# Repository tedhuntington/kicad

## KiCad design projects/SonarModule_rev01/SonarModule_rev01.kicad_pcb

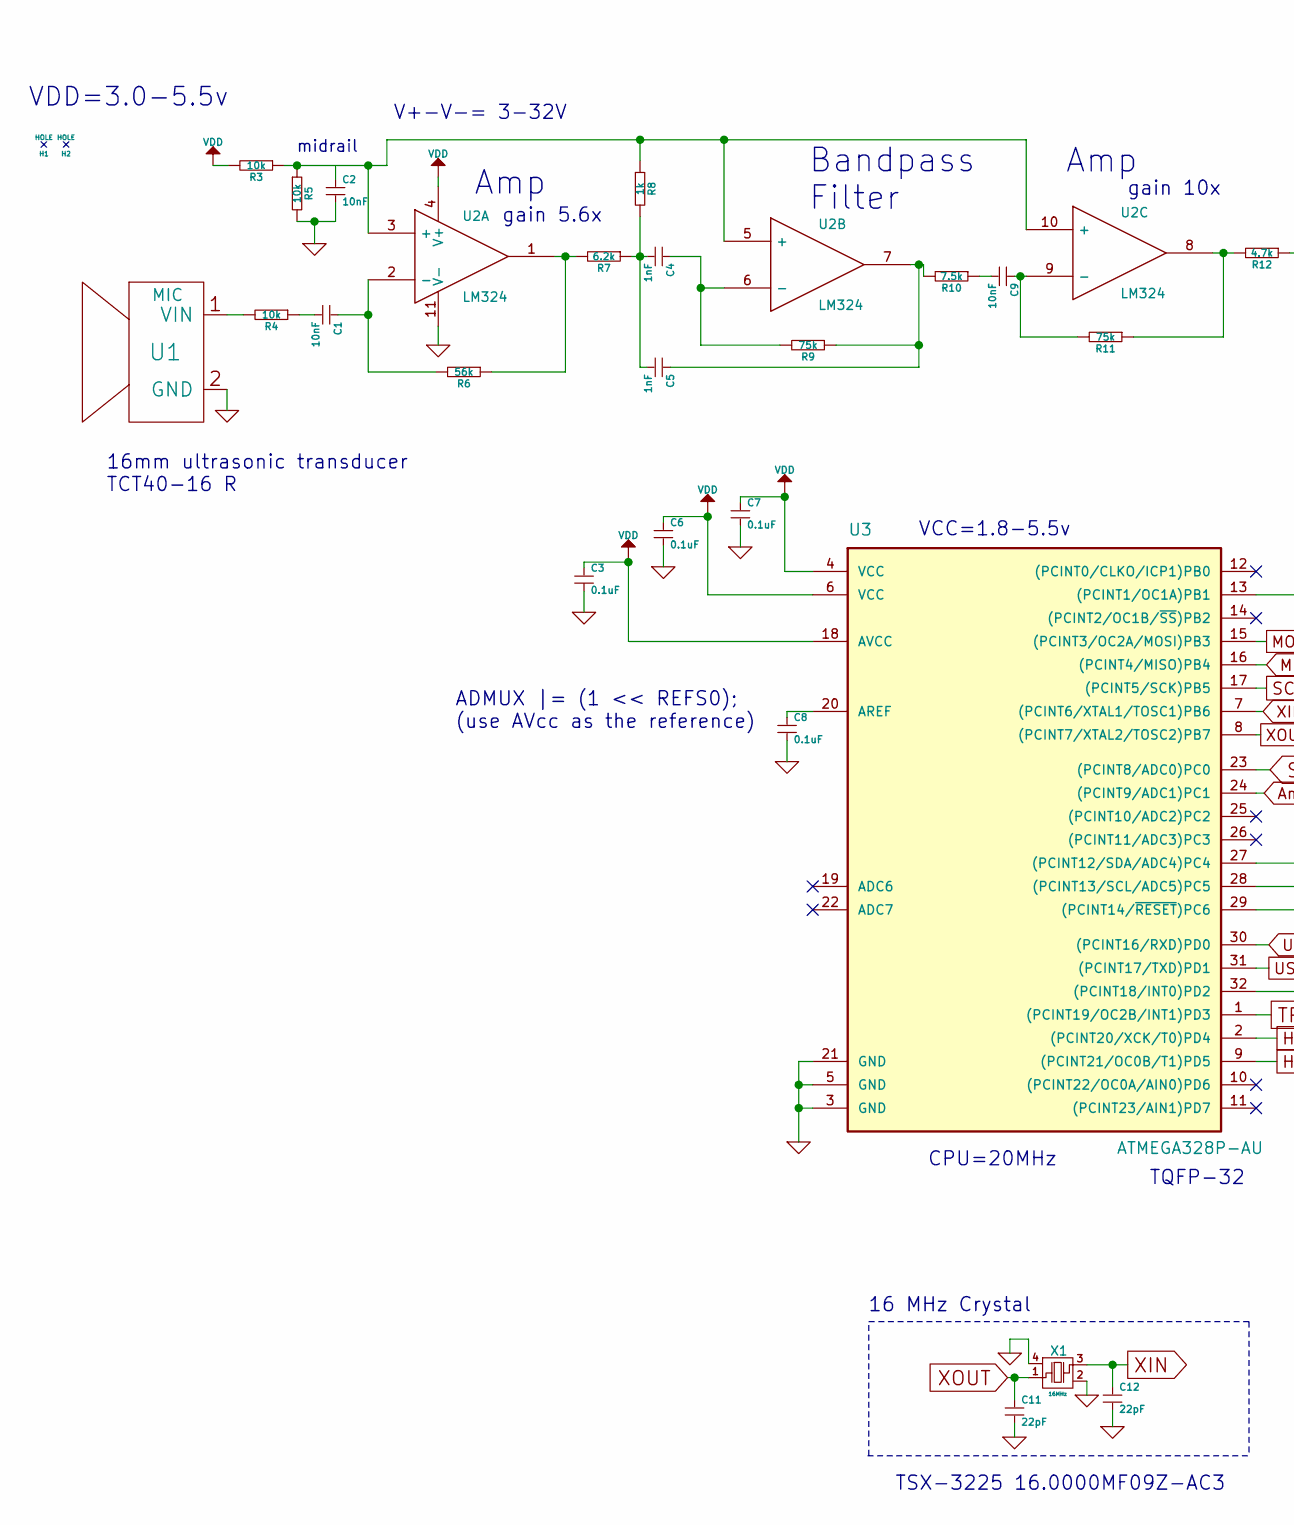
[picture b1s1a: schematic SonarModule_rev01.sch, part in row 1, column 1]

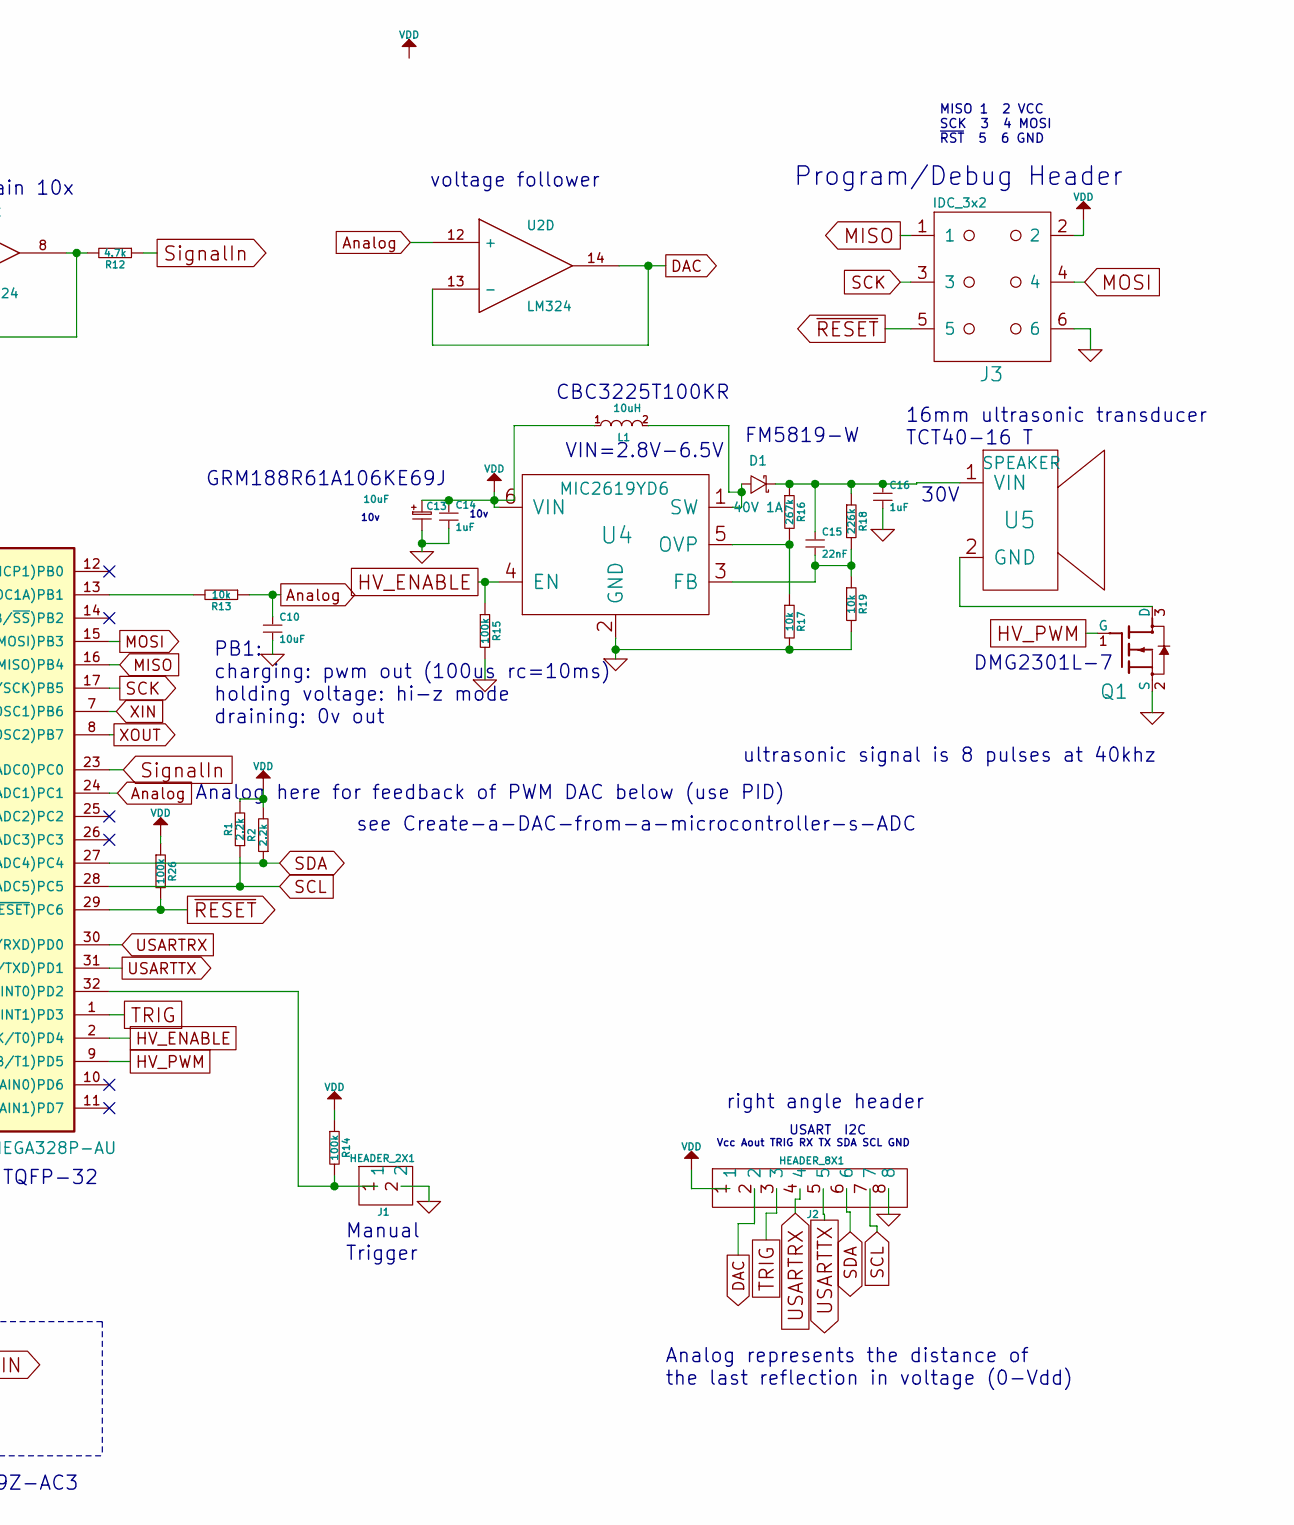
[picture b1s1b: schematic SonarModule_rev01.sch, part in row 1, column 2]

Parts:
C1, C2, C9: 10nF; TED_SM1608_0603_C
C3, C6, C7, C8: 0.1uF; TED_SM1608_0603_C
C4, C5: 1nF; TED_SM1608_0603_C
C10, C13: 10uF; TED_SM1608_0603_C
C11, C12: 22pF; TED_SM1608_0603_C
C14, C16: 1uF; TED_SM1608_0603_C
C15: 22nF; TED_SM1608_0603_C
D1: 40V 1A; TED_DO-214AC
H1, H2: HOLE; TED_Hole_3mm
J1: HEADER_2X1; TED_HEADER_2x1
J2: HEADER_8X1; TED_HEADER_8x1
J3: IDC_3x2; TED_HEADER_3x2
L1: 10uH; L_3225_1210
Q1: NMOSFET_GSD; SOT-23
R1, R2: 2.2k; TED_SM0603_R
R3, R4, R5, R13, R17, R19: 10k; TED_SM0603_R
R6: 56k; TED_SM0603_R
R7: 6.2k; TED_SM0603_R
R8: 1k; TED_SM0603_R
R9, R11: 75k; TED_SM0603_R
R10: 7.5k; TED_SM0603_R
R12: 4.7k; TED_SM0603_R
R14, R15, R26: 100k; TED_SM0603_R
R16: 267k; TED_SM0603_R
R18: 226k; TED_SM0603_R
U1: MIC; Transducer_16mm
U2: LM324; SOIC-14_3.9x8.7mm_Pitch1.27mm
U3: ATMEGA328P-AU; TQFP-32_7x7mm_Pitch0.8mm
U4: MIC2619YD6; SOT-23-6
U5: SPEAKER; Transducer_16mm
X1: 16MHz; TED_crystal_FA-20H

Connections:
Analog: C10.1, R13.1, U2.12 (+), U3.24 ((PCINT9/ADC1)PC1)
DAC: J2.2, U2.13 (-), U2.14
GND: C2.2, C3.2, C6.2, C7.2, C8.2, C10.2, C11.2, C12.2, C13.2, C14.2, C16.2, J1.2, J2.8, J3.6, Q1.2 (S), R5.2, R15.2, R17.2, R19.2, U1.2 (GND), U2.11 (V-), U3.3 (GND), U3.5 (GND), U3.21 (GND), U4.2 (GND), X1.2, X1.4
HV_ENABLE: R15.1, U3.2 ((PCINT20/XCK/T0)PD4), U4.4 (EN)
HV_PWM: Q1.1 (G), U3.9 ((PCINT21/OC0B/T1)PD5)
MISO: J3.1, U3.16 ((PCINT4/MISO)PB4)
MOSI: J3.4, U3.15 ((PCINT3/OC2A/MOSI)PB3)
unnamed: C1.1, R6.2, U2.2 (-)
unnamed: C1.2, R4.1
unnamed: C4.1, R9.2, U2.6 (-)
unnamed: C4.2, C5.2, R7.1, R8.2
unnamed: C5.1, R9.1, R10.2, U2.7
unnamed: C8.1, U3.20 (AREF)
unnamed: C9.1, R11.2, U2.9 (-)
unnamed: C9.2, R10.1
unnamed: C15.1, C16.1, D1.2 (K), R16.1, R18.1, U5.1 (VIN)
unnamed: C15.2, R18.2, R19.1, U4.3 (FB)
unnamed: D1.1 (A), L1.2, U4.1 (SW)
unnamed: J1.1, R14.2, U3.32 ((PCINT18/INT0)PD2)
unnamed: Q1.3 (D), U5.2 (GND)
unnamed: R3.1, R5.1, R8.1, U2.3 (+), U2.5 (+), U2.10 (+)
unnamed: R4.2, U1.1 (VIN)
unnamed: R6.1, R7.2, U2.1
unnamed: R11.1, R12.2, U2.8
unnamed: R13.2, U3.13 ((PCINT1/OC1A)PB1)
unnamed: R16.2, R17.1, U4.5 (OVP)
SCK: J3.3, U3.17 ((PCINT5/SCK)PB5)
SCL: J2.7, R1.1, U3.28 ((PCINT13/SCL/ADC5)PC5)
SDA: J2.6, R2.1, U3.27 ((PCINT12/SDA/ADC4)PC4)
SignalIn: R12.1, U3.23 ((PCINT8/ADC0)PC0)
TRIG: J2.3, U3.1 ((PCINT19/OC2B/INT1)PD3)
USARTRX: J2.4, U3.30 ((PCINT16/RXD)PD0)
USARTTX: J2.5, U3.31 ((PCINT17/TXD)PD1)
VDD: C3.1, C6.1, C7.1, C13.1, C14.1, J2.1, J3.2, L1.1, R1.2, R2.2, R3.2, R14.1, R26.1, U2.4 (V+), U3.4 (VCC), U3.6 (VCC), U3.18 (AVCC), U4.6 (VIN)
XIN: C12.1, U3.7 ((PCINT6/XTAL1/TOSC1)PB6), X1.3
XOUT: C11.1, U3.8 ((PCINT7/XTAL2/TOSC2)PB7), X1.1
~RESET~: J3.5, R26.2, U3.29 ((PCINT14/~RESET~)PC6)

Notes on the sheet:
VDD=3.0-5.5v
16 MHz Crystal
USART
MISO 1 2 VCC SCK 3 4 MOSI ~RST~ 5 6 GND
Program/Debug Header
Vcc Aout TRIG RX TX SDA SCL GND
Manual Trigger
I2C
VIN=2.8V-6.5V
30V
Amp
Bandpass Filter
midrail
voltage follower
gain 5.6x
gain 10x
ultrasonic signal is 8 pulses at 40khz
Analog represents the distance of the last reflection in voltage (0-Vdd)
ADMUX |= (1 << REFS0); (use AVcc as the reference)
Analog here for feedback of PWM DAC below (use PID)
see Create-a-DAC-from-a-microcontroller-s-ADC
PB1: charging: pwm out (100us rc=10ms) holding voltage: hi-z mode draining: 0v out
right angle header
16mm ultrasonic transducer TCT40-16 T
16mm ultrasonic transducer TCT40-16 R
CBC3225T100KR
FM5819-W
GRM188R61A106KE69J
DMG2301L-7
CPU=20MHz
TQFP-32
VCC=1.8-5.5v
V+-V-= 3-32V
10v
TSX-3225 16.0000MF09Z-AC3

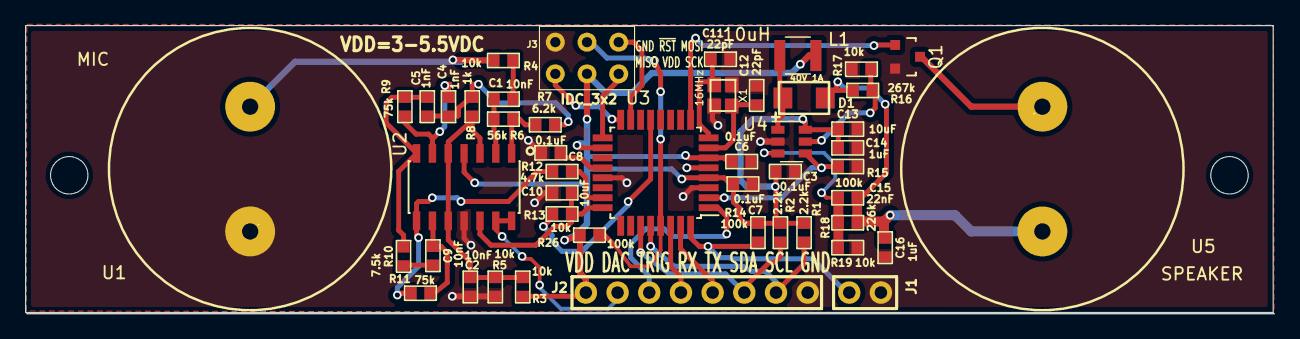
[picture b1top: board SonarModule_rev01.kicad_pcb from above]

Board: 2 copper layers, 100.0 x 23.0 mm, 50 parts (0 on the bottom side), 37 nets.

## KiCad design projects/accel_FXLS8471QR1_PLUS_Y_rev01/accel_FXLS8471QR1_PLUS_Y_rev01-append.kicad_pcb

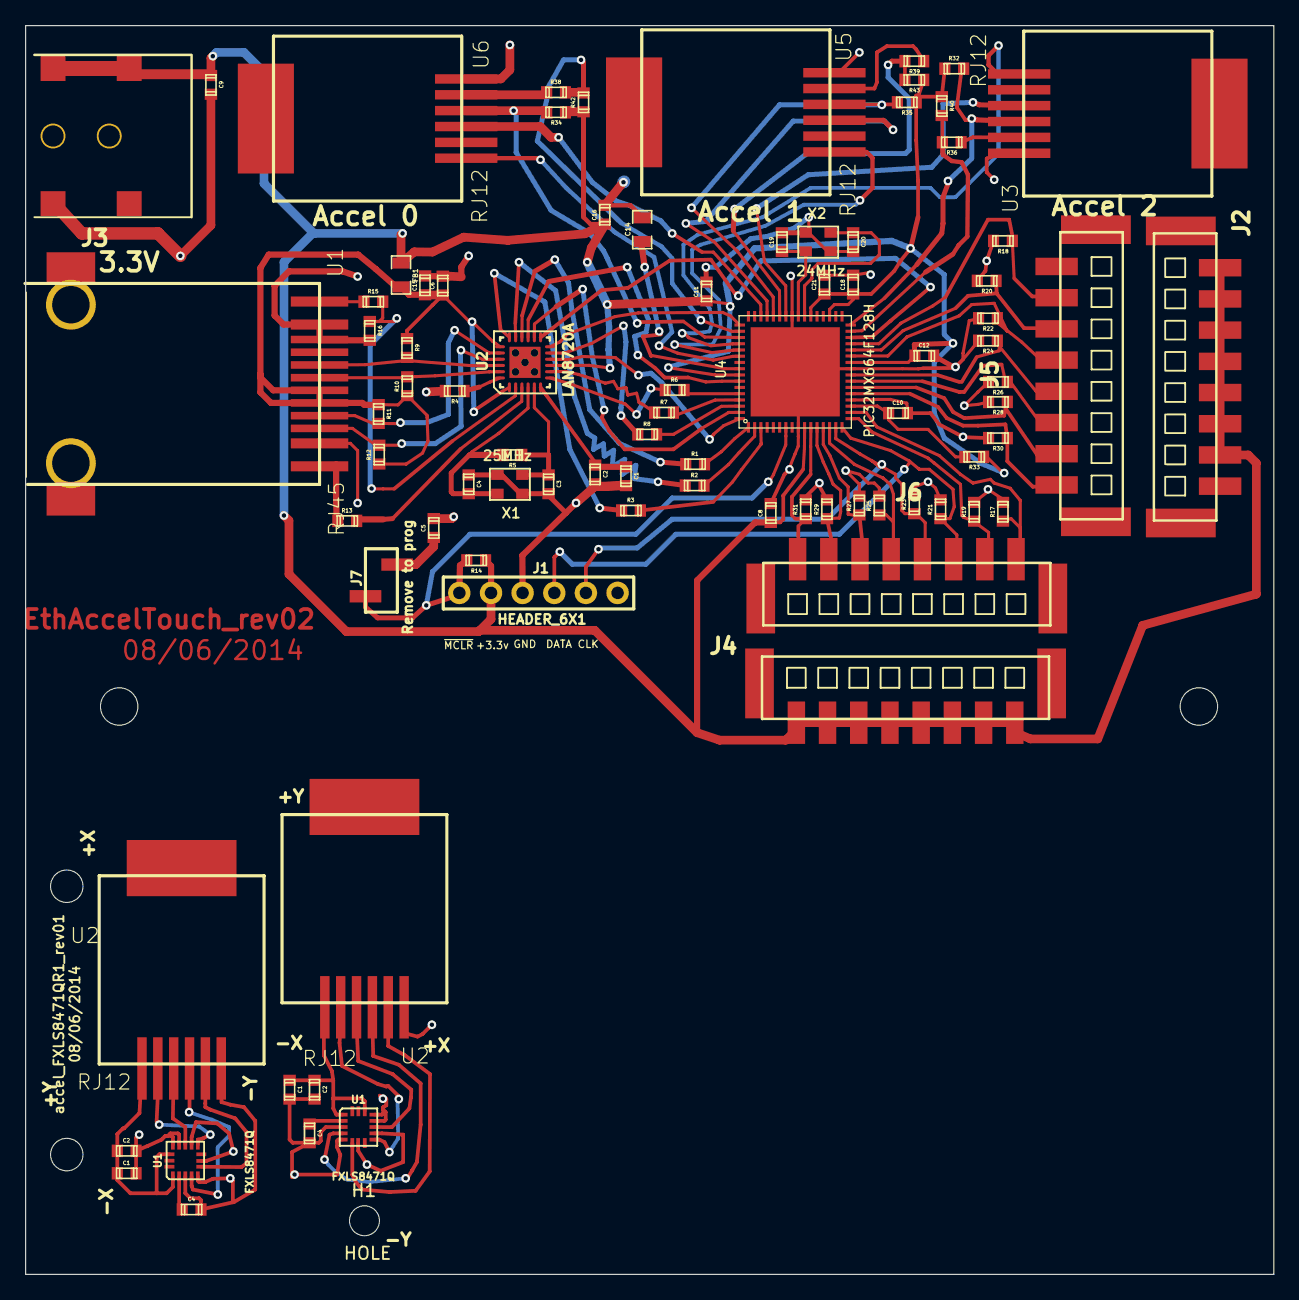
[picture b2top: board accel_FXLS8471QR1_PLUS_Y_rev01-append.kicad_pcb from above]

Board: 2 copper layers, 100.0 x 100.0 mm, 90 parts (0 on the bottom side), 73 nets.

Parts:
C1, C2#2, C2#3, C4#2, C4#3, C5, C6, C8, C10, C11, C12, C16, C18, C21: .1uF; TED_SM0603
C1#2, C1#3, C2, C15: 1uF; TED_SM0603
C3, C4: 18pF; TED_SM0603
C9: 4.7uF; TED_SM0603
C14: 10uF; TED_SM0805
C19, C20: 9pF; TED_SM0603
FB1: 500mA; TED_SM0805
H1, H2: HOLE; TED_Hole_3mm
H1#2, H2#2: HOLE; TED_Hole_2_6mm
H1#3: HOLE; TED_Hole_2_4mm
J1: HEADER_6X1; TED_HEADER_6x1_BOTTOM
J2, J4, J5, J6: TERMINAL_8X1; TED_Terminal_8x1_1814760
J3: DC_2.1MM; TED_DC_2.1mm_SMT
J7: Remove to prog; TED_JUMPER_2x1_SMD
R1, R2, R3, R6, R7, R8, R36, R38, R39: 33; TED_SM0603
R4: 12.1k 1%; TED_SM0603
R5: 1M; TED_SM0603
R9, R10, R11, R12: 49.9; TED_SM0603
R13, R15: 249; TED_SM0603
R14: 4.7k; TED_SM0603
R16: 10k 1%; TED_SM0603
R17, R18, R19, R20, R21, R22, R23, R24, R25, R26, R27, R28, R29, R30, R31: 1k; TED_SM0603
R32, R34, R35, R40, R42, R43: 2.4k; TED_SM0603
R33: 10; TED_SM0603
U1: RJ45; TED_RJ45_12pin_SMD
U1#2, U1#3: FXLS8471Q; TED_QFN16_3x5
U2: LAN8720A; TED_QFN24
U2#2, U2#3, U3, U5, U6: RJ12; TED_RJ12_855135002
U4: PIC32MX664F128H; TED_QFN64+1
X1: 25MHz; TED_crystal_TSX3225
X2: 24MHz; TED_crystal_TSX3225

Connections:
+3.3v: C8.1, C9.1, C11.1, C12.1, C16.1, C18.1, C21.1, FB1.1, J1.2, J2.1, J2.2, J2.3, J2.4, J2.5, J2.6, J2.7, J3.1, J4.1, J4.2, J4.3, J4.4, J4.5, J4.6, J4.7, J4.8, R14.1, R32.1, R33.1, R34.1, R35.1, R40.1, R42.1, R43.1, U2.9, U4.10, U4.26, U4.35, U4.38, U4.57
ACCEL1_VDD: U4.54, U6.6
ACCEL2_VDD: U4.53, U5.6
ACCEL3_VDD: U3.6, U4.52
AVDD: C6.1, C15.1, FB1.2, R9.1, R10.1, R11.1, R12.1, U1.5, U1.6, U2.1, U2.19
ECRSDV: R8.2, U4.62
EMDC: U2.13, U4.30
EMDIO: U2.12, U4.49
EREFCLK: U2.14, U4.63
ERXD0: R7.2, U4.61
ERXD1: R6.2, U4.60
ERXERR: U2.10, U4.64
ETXD0: R2.2, U4.2
ETXD1: R3.2, U4.3
ETXEN: R1.2, U4.1
GND: C1.2, C1#2.2, C1#3.2, C2.2, C2#2.2, C2#3.2, C3.2, C4.1, C4#2.2, C4#3.2, C5.2, C6.2, C8.2, C9.2, C10.2, C11.2, C12.2, C14.2, C15.2, C16.2, C18.2, C19.2, C20.2, C21.2, J1.3, J3.2, R4.2, R16.2, R17.2, R18.2, R19.2, R20.2, R21.2, R22.2, R23.2, R24.2, R25.2, R26.2, R27.2, R28.2, R29.2, R30.2, R31.2, U1.2, U1.10, U1.11, U1#2.3, U1#2.5, U1#2.7, U1#2.10, U1#2.12, U1#2.13, U1#3.3, U1#3.5, U1#3.7, U1#3.10, U1#3.12, U1#3.13, U2.25, U2#2.1, U2#3.1, U3.1, U4.9, U4.20, U4.25, U4.41, U4.65, U5.1, U6.1, X1.2, X1.4, X2.2, X2.4
GreenLED: R15.1, U1.12
ICSPCLK_RB1: J1.5, J6.5, R23.1, U4.15
ICSPDAT_RB0: J1.4, J6.6, R21.1, U4.16
INT0: U4.46, U6.4
INT1: U1#2.11, U1#3.11, U2#2.4, U2#3.4, U3.4, U4.42
INT2: U1#2.9, U1#3.9, U2#2.5, U2#3.5
INT4: U4.45, U5.4
unnamed: C4#2.1, C4#3.1, U1#2.2, U1#3.2
unnamed: C19.1, U4.40, X2.1
unnamed: R15.2, R16.1, U2.2
unnamed: R4.1, U2.24
unnamed: R13.2, U2.3
unnamed: R7.1, U2.8
unnamed: R6.1, U2.7
unnamed: C20.1, U4.39, X2.3
unnamed: C5.1, J7.2
unnamed: C3.1, R5.1, U2.5, X1.1
unnamed: C10.1, R33.2, U4.19
unnamed: R1.1, U2.16
unnamed: R2.1, U2.17
unnamed: R3.1, U2.18
unnamed: C4.2, R5.2, U2.4, X1.3
unnamed: C1.1, C2.1, U2.6
unnamed: R8.1, U2.11
unnamed: C14.1, U4.56
unnamed: R39.1, U5.2
unnamed: R38.1, U6.2
unnamed: R36.1, U3.2
RB2: J6.4, R25.1, U4.14
RB3: J6.3, R27.1, U4.13
RB4: J6.2, R29.1, U4.12
RB5: J6.1, R31.1, U4.11
RB6: J6.7, R19.1, U4.17
RB7: J6.8, R17.1, U4.18
RB8: J5.1, R30.1, U4.21
RB9: J5.2, R28.1, U4.22
RB10: J5.3, R26.1, U4.23
RB11: J5.4, R24.1, U4.24
RB12: J5.5, R22.1, U4.27
RB13: J5.6, R20.1, U4.28
RB14: J5.7, R18.1, U4.29
RXN: R9.2, U1.8, U2.22
RXP: R10.2, U1.7, U2.23
SCL: U1#2.4, U1#3.4, U2#2.3, U2#3.3
SCL1: R35.2, U4.44, U5.3
SCL3: R34.2, U4.51, U6.3
SCL5: R32.2, U3.3, U4.32
SDA: U1#2.6, U1#3.6, U2#2.2, U2#3.2
SDA1: R39.2, R43.2, U4.43
SDA3: R38.2, R42.2, U4.50
SDA5: R36.2, R40.2, U4.31
TXN: R11.2, U1.4, U2.20
TXP: R12.2, U1.3, U2.21
Vdd: C1#2.1, C1#3.1, C2#2.1, C2#3.1, U1#2.1, U1#2.14, U1#3.1, U1#3.14, U2#2.6, U2#3.6
YellowLED: R13.1, U1.1
nRST: U2.15, U4.58
~MCLR~: J1.1, J7.1, R14.2, U4.7

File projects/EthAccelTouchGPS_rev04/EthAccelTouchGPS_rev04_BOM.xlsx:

EthAccelTouchGPS_rev04
Sat 24 Sep 2016 09:21:54 PM PDT
Eeschema 4.0.3+e1-6302~38~ubuntu14.04.1-stable
Component Count:95
Ref | Qnty | Value | Part | Part# | Unit Cost | Total Cost | Major Distributor | Minor Distributor
C11, C21, C12, C8, C16, C6, C18, C10, C1, C5, C7, | 11 | .1uF | capacitors:SM1608_0603_C | Vj0603V104ZXAPW1BC | 0.1 | 1.1 | Mouser
C13, C14, | 2 | 15pF | capacitors:SM1608_0603_C | GRM1885C1H150JA01D | 0.1 | 0.2 | Mouser
C2, C15, | 2 | 1uF | capacitors:SM1608_0603_C | GRM188R61E105KA12D | 0.1 | 0.2 | Digi-Key
C4, C3, | 2 | 16pF | capacitors:SM1608_0603_C | GRM1885C1H160JA01D | 0.1 | 0.2 | Mouser
C9, | 1 | 4.7uF | capacitors:SM1608_0603_C | C0603C475K9PACTU | 0.13 | 0.13 | Mouser
D1, | 1 | LED | led:SM1206_LED | APTR3216SGC | 0.15 | 0.15 | Mouser
FB1, | 1 | 500mA | resistors:SM0805_R | MPZ2012S601A | 0.12 | 0.12 | Mouser
H1, H2, H3, H4, | 4 | HOLE | holes:Hole_3mm |  | 0 | 0
J1 | 1 | HEADER_6X1 | connectors:HEADER_6x1 | 640456-6 | 0.27 | 0.27 | Mouser
J3, | 1 | TERMINAL_2X1 | connectors:TERMINAL_SPRING_2.54MM_2PIN_1989748 | 1989748 | 0.28 | 0.28 | Mouser
J4, J6, J5, J2, | 4 | TERMINAL_8X1 | connectors:Terminal_8x1_1814760 | 1814760 | 1.31 | 5.24 | Mouser
J7, | 1 | JUMPER_2X1 | connectors:JUMPER_2x1_SMD | M20-8770242 | 0.2 | 0.2 | Mouser
J8 | 1 | HEADER_6X1 | connectors:TERMINAL_SPRING_2.54MM_6PIN_1989780 | 1989780 | 0.77 | 0.77 | Digi-Key/Mouser
P1, P4, P6, P5, P3, P2, P7, P8, P9, P10, P11, P12, | 12 | TEST_PAD | test_pads:TEST_PAD |  | 0 | 0
Q1, | 1 | NMOSFET_GSD | transistors:SOT-23 | 68000-102HLF | 0.36 | 0.36 | Mouser
R14, | 1 | 4.7k | resistors:SM0603_R | ERJ-3EKF4701V | 0.1 | 0.1 | Digi-Key
R15, R13, R5, | 3 | 249 | resistors:SM0603_R | ERJ-2RKF2490X | 0.1 | 0.3 | Mouser/Digi-Key
R16, | 1 | 10k 1% | resistors:SM0603_R | ERJ-3EKF1001V | 0.1 | 0.1 | Digi-Key
R17, R19, R21, R23, R25, R27, R29, R31, R18, R20, R22, R24, R26, R28, R30, | 15 | 1k | resistors:SM0603_R | ERJ-3EKF1002V | 0.1 | 1.5 | Digi-Key
R33, | 1 | 10 | resistors:SM0603_R | CRCW060310R0FKEA | 0.1 | 0.1 | Digi-Key/Mouser
R34, R42, R35, R43, R32, R40, | 6 | 2.4k | resistors:SM0603_R | RC0603FR-072K4L | 0.1 | 0.6 | Digi-Key/Mouser
R37, | 1 | 1M | resistors:SM0603_R | ERJ-3EKF1004V | 0.1 | 0.1 | Digi-Key
R4, | 1 | 12.1k 1% | resistors:SM0603_R | ERJ-6ENF1212V | 0.1 | 0.1 | Mouser
R7, R6, R2, R1, R3, R8, R38, R39, R36, | 9 | 33 | resistors:SM0603_R | RC0603FR-0733RL | 0.1 | 0.9 | Digi-Key/Mouser
R9, R10, R11, R12, | 4 | 49.9 | resistors:SM0603_R | ERJ-3EKF49R9V | 0.1 | 0.4 | Digi-Key
U1, | 1 | RJ45_12_PIN | connectors:RJ45_12pin_Top | HR911105A | 0.85 | 0.85 |  | AliExpress
U2, | 1 | LAN8720A/LAN8720AI | ICs:QFN24+1 | LAN8720A | 1.49 | 1.49 | Digi-Key
U4, | 1 | PIC32MZ0512EFE064_QFN | ICs:QFN64+1H | PIC32MZ0512EFE064-I/MR | 7.86 | 7.86 | MicrochipDirect
U6, U5, U3, | 3 | RJ12 | connectors:RJ12_855135002 | 855135002 | 0.98 | 2.94 | Mouser
X1, | 1 | 25MHz | crystals:crystal_FA-20H | FA-20H 25.0000MF20X-K3 | 0.73 | 0.73 | Mouser
X2, | 1 | 24MHz | crystals:crystal_TSX3225 | TSX-3225 24.0000MF20G-AC3 | 0.51 | 0.51 | Mouser
Total |  |  |  |  |  | 27.8

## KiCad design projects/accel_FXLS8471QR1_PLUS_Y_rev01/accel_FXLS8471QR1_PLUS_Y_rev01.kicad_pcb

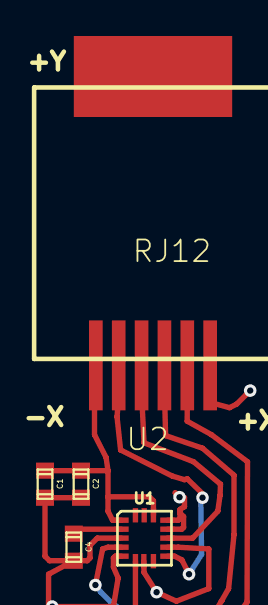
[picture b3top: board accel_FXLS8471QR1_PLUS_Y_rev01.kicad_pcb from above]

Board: 2 copper layers, 6 parts (0 on the bottom side), 7 nets.

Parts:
C1: 1uF; TED_SM0603
C2, C4: .1uF; TED_SM0603
H1: HOLE; TED_Hole_2_4mm
U1: FXLS8471Q; TED_QFN16_3x5
U2: RJ12; TED_RJ12_855135002

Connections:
GND: C1.2, C2.2, C4.2, U1.3, U1.5, U1.7, U1.10, U1.12, U1.13, U2.1
INT1: U1.11, U2.4
INT2: U1.9, U2.5
unnamed: C4.1, U1.2
SCL: U1.4, U2.3
SDA: U1.6, U2.2
Vdd: C1.1, C2.1, U1.1, U1.14, U2.6
